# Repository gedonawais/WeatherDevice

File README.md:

# Weather Device - Raspberry Pi Zero 2W Setup Guide

This document explains how to set up the Raspberry Pi Zero 2W for the Weather Device project.

---

# 1. Install Raspberry Pi OS Lite (64 Bit) without Desktop

1. Download and install **Raspberry Pi OS Lite** using Raspberry Pi Imager.
2. Flash the OS to the SD card.
3. Before writing the image, configure:
   - Set username and password
   - Configure Wi-Fi (optional)

Boot the Raspberry Pi.

---

# 2. Configure Raspberry Pi

## 2.1 Enable Automatic Login

Open the Raspberry Pi configuration tool:

```bash
sudo raspi-config
```
Set System Date and Time and WLAN Country in the Localisation menu if not setup during installaion of RPi image

Set Wireless LAN SSID and Password (for wifi)

Navigate to:
```
System Options
    → Auto Login
        → Console Autologin
```

Select console auto login.

This allows the Raspberry Pi to automatically log in after boot.

---

## 2.2 Disable sudo Password Requirement

Navigate to:
```
System Options
    → Admin Password
        → Disable
```

This allows scripts and services to execute sudo commands without requiring a password.

---

# 3. Configure Network

## 3.1 Connect to Wi-Fi

Open Raspberry Pi configuration:

```bash
sudo raspi-config
```

Navigate to:

```
System Options
    → Wireless LAN
```

Enter:

- Wi-Fi SSID
- Wi-Fi password

Reboot if required.

---

# 4. Install Required Software

## 4.1 Update Package List

Run:

```bash
sudo apt update
```

---

## 4.2 Install Git

Install Git:

```bash
sudo apt install git -y
```

Verify installation:

```bash
git --version
```

---

# 5. Download Weather Device Repository
If you wish to enable Wifi use the following commands

```bash
sudo systemctl enable NetworkManager.service
sudo systemctl start NetworkManager.service
sudo nmcli radio wifi on
```
Move to the home directory:

```bash
cd /home
```

Clone the repository:

```bash
sudo git clone <REPOSITORY_URL>
```

Example:

```bash
sudo git clone https://github.com/<username>/WeatherDevice.git
```

The project should now be available at:

```
/home/WeatherDevice
```

---

# 6. Configure Git Repository Permission

If Git shows a **"detected dubious ownership in repository"** error, run:

```bash
git config --global --add safe.directory /home/WeatherDevice
```

---

# 7. Deploy System Configuration

Run the configuration deployment script:

```bash
bash /home/WeatherDevice/Firmware/RPi/Installations/deploy_config.sh
```

This installs required system files, services, and configurations.

---

# 8. Install Python Dependencies

Run the installation script:

```bash
bash /home/WeatherDevice/Firmware/RPi/Installations/install.sh
```

This installs all required libraries and dependencies.

---

# 9. Disable Wi-Fi (Optional)
NetworkManager is already disabled so no need to run this
Disable Wi-Fi:

```bash
sudo nmcli radio wifi off
```

Check Wi-Fi status:

```bash
nmcli radio
```

---

---

# Restart Raspberry Pi

Reboot the device:

```bash
sudo reboot
```

Wait until the Raspberry Pi boots again.

---

# 10. Weather Service Management

## Start Weather Service

```bash
sudo systemctl enable weather.service
sudo systemctl start weather.service
```

---

# 12. Check Service Status

```bash
sudo systemctl status weather.service
```

---

## View Live Service Logs

To monitor real-time logs:

```bash
journalctl -u weather.service -f
```

---

## Restart Service if there are any issues in logs

After changing code:

```bash
sudo systemctl restart weather.service
```

---

## Updating the Software

To update the Weather Device software:

```bash
sudo nmcli radio wifi on
cd /home/WeatherDevice
```

Download the latest changes:

```bash
sudo git pull
sudo nmcli radio wifi off
```

Restart the service:

```bash
sudo systemctl restart weather.service
```

# Setup Complete

The Raspberry Pi Zero 2W is now configured and ready to run the Weather Device application.

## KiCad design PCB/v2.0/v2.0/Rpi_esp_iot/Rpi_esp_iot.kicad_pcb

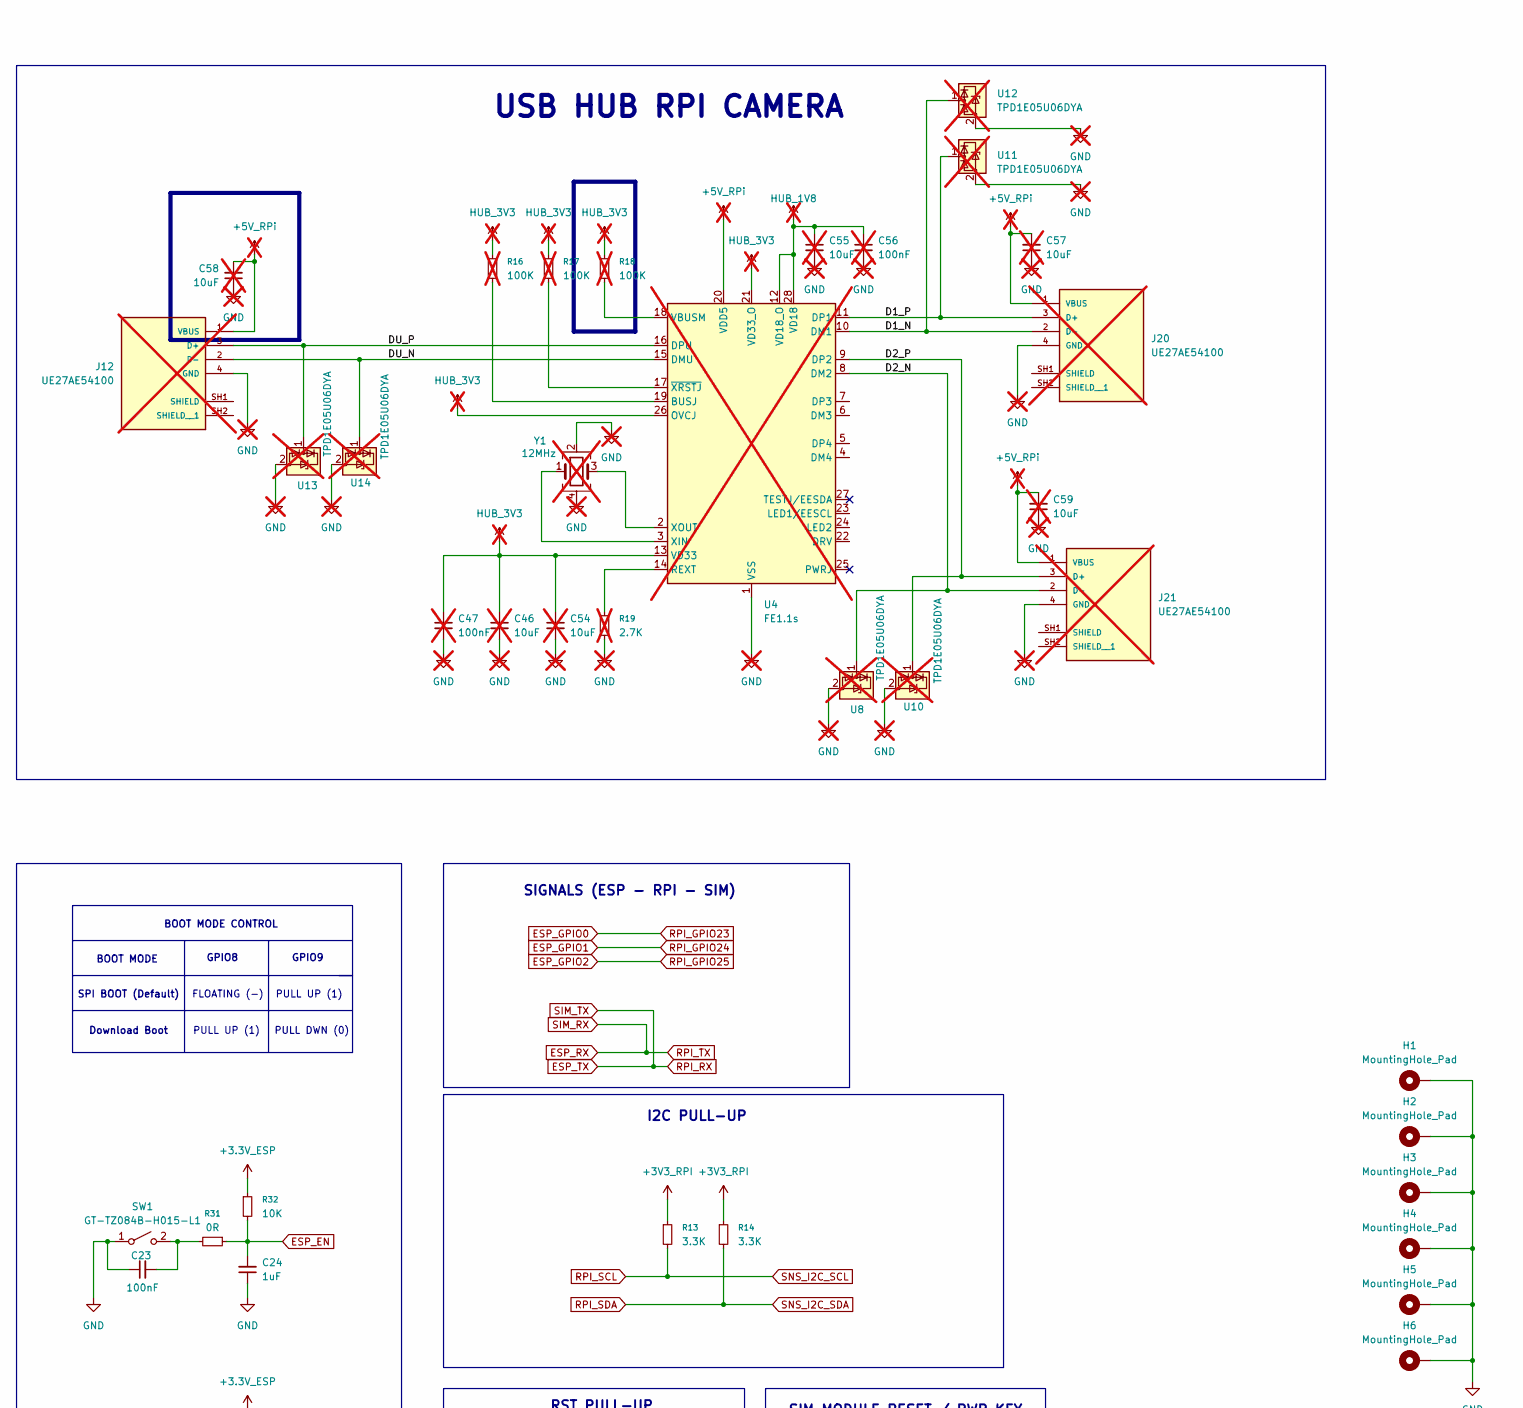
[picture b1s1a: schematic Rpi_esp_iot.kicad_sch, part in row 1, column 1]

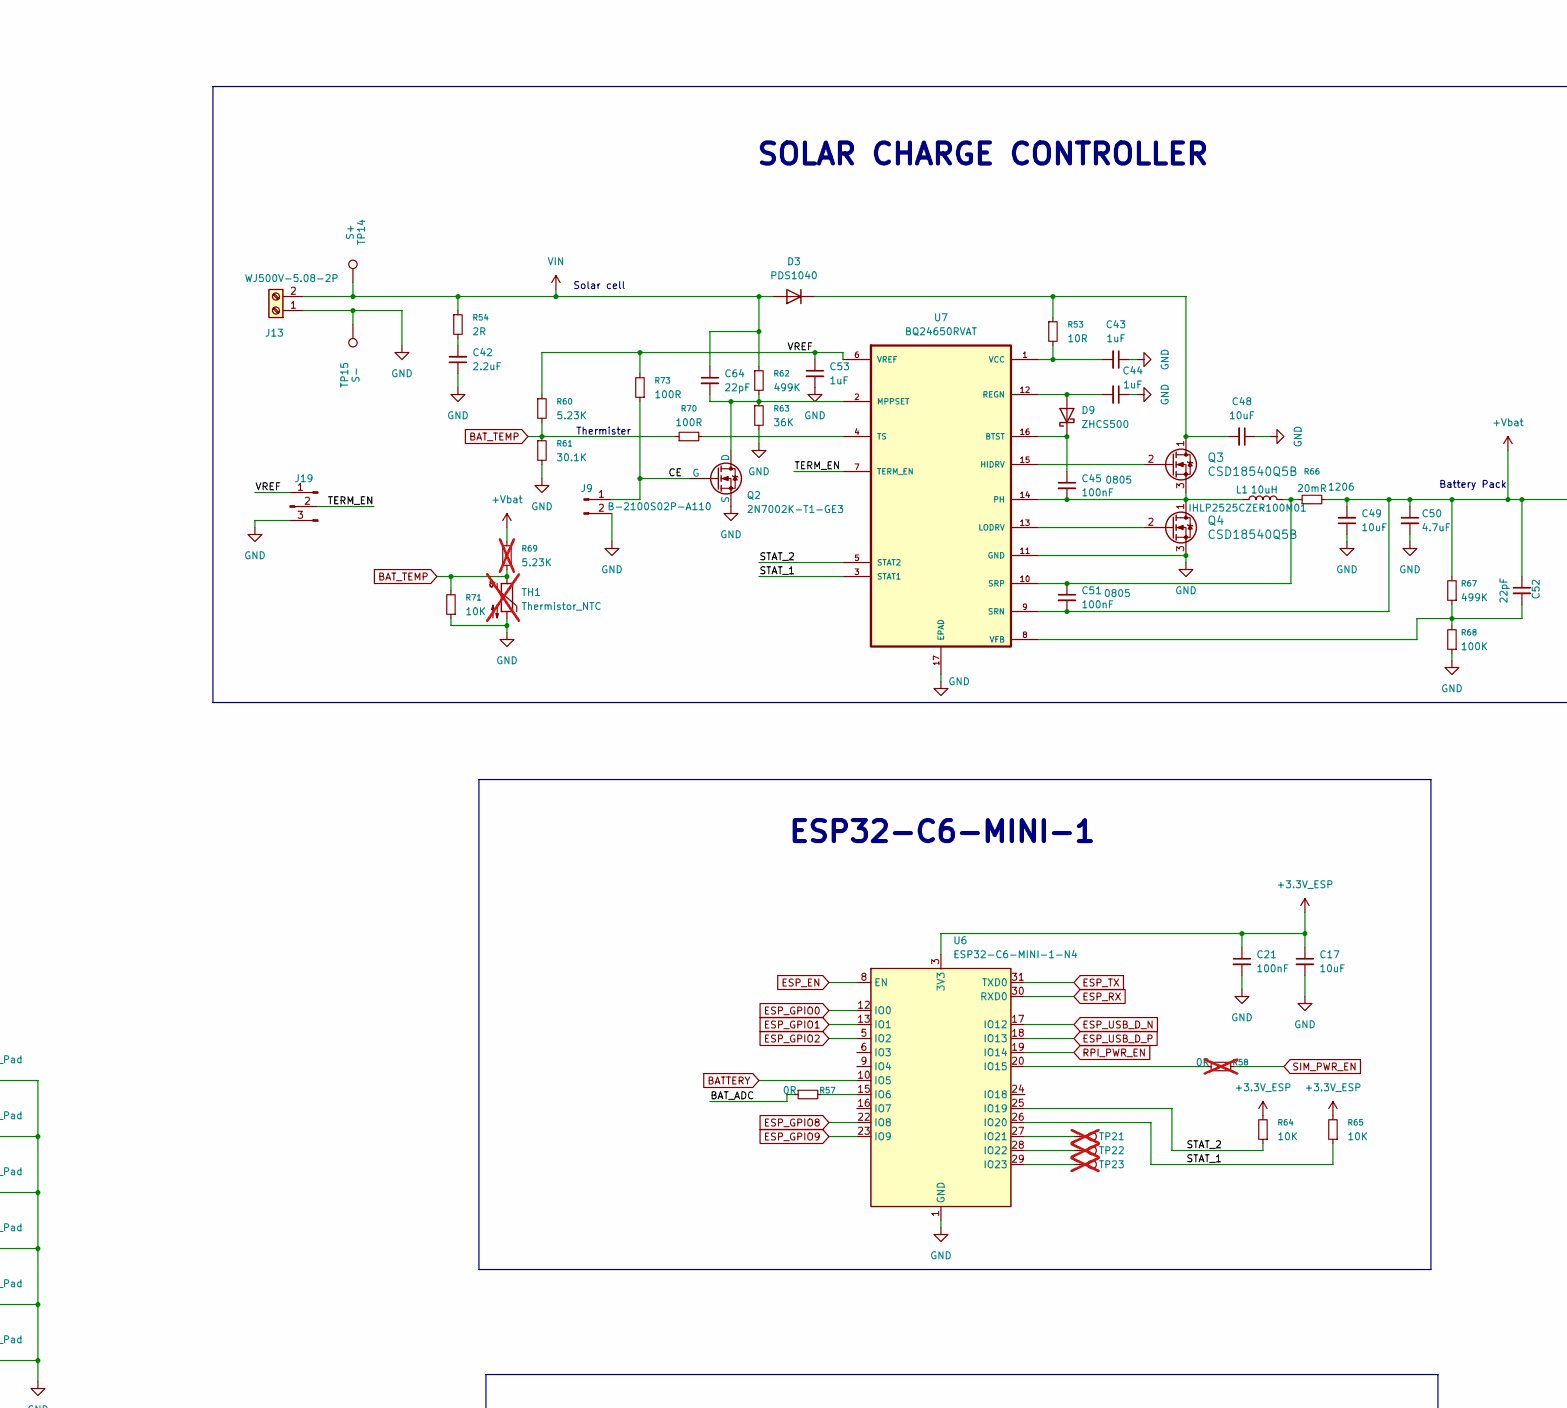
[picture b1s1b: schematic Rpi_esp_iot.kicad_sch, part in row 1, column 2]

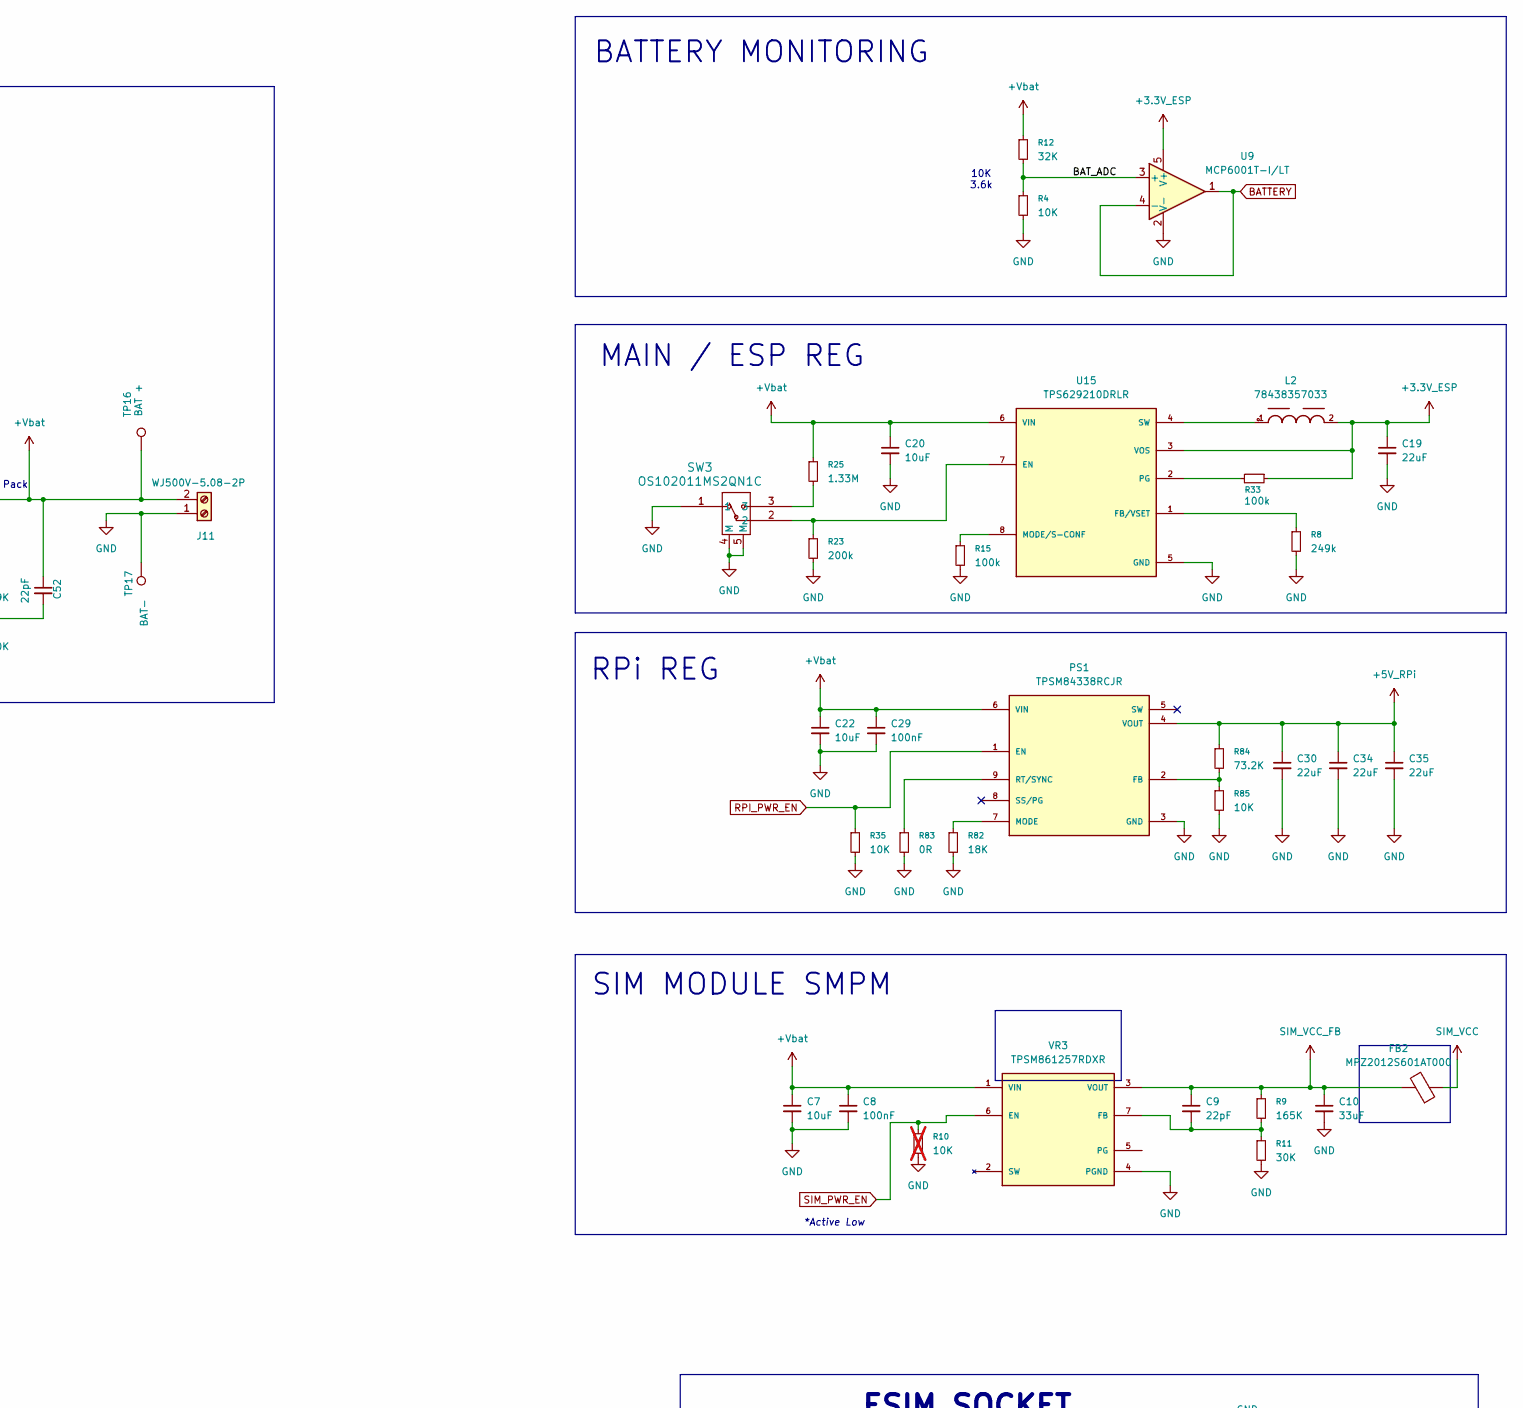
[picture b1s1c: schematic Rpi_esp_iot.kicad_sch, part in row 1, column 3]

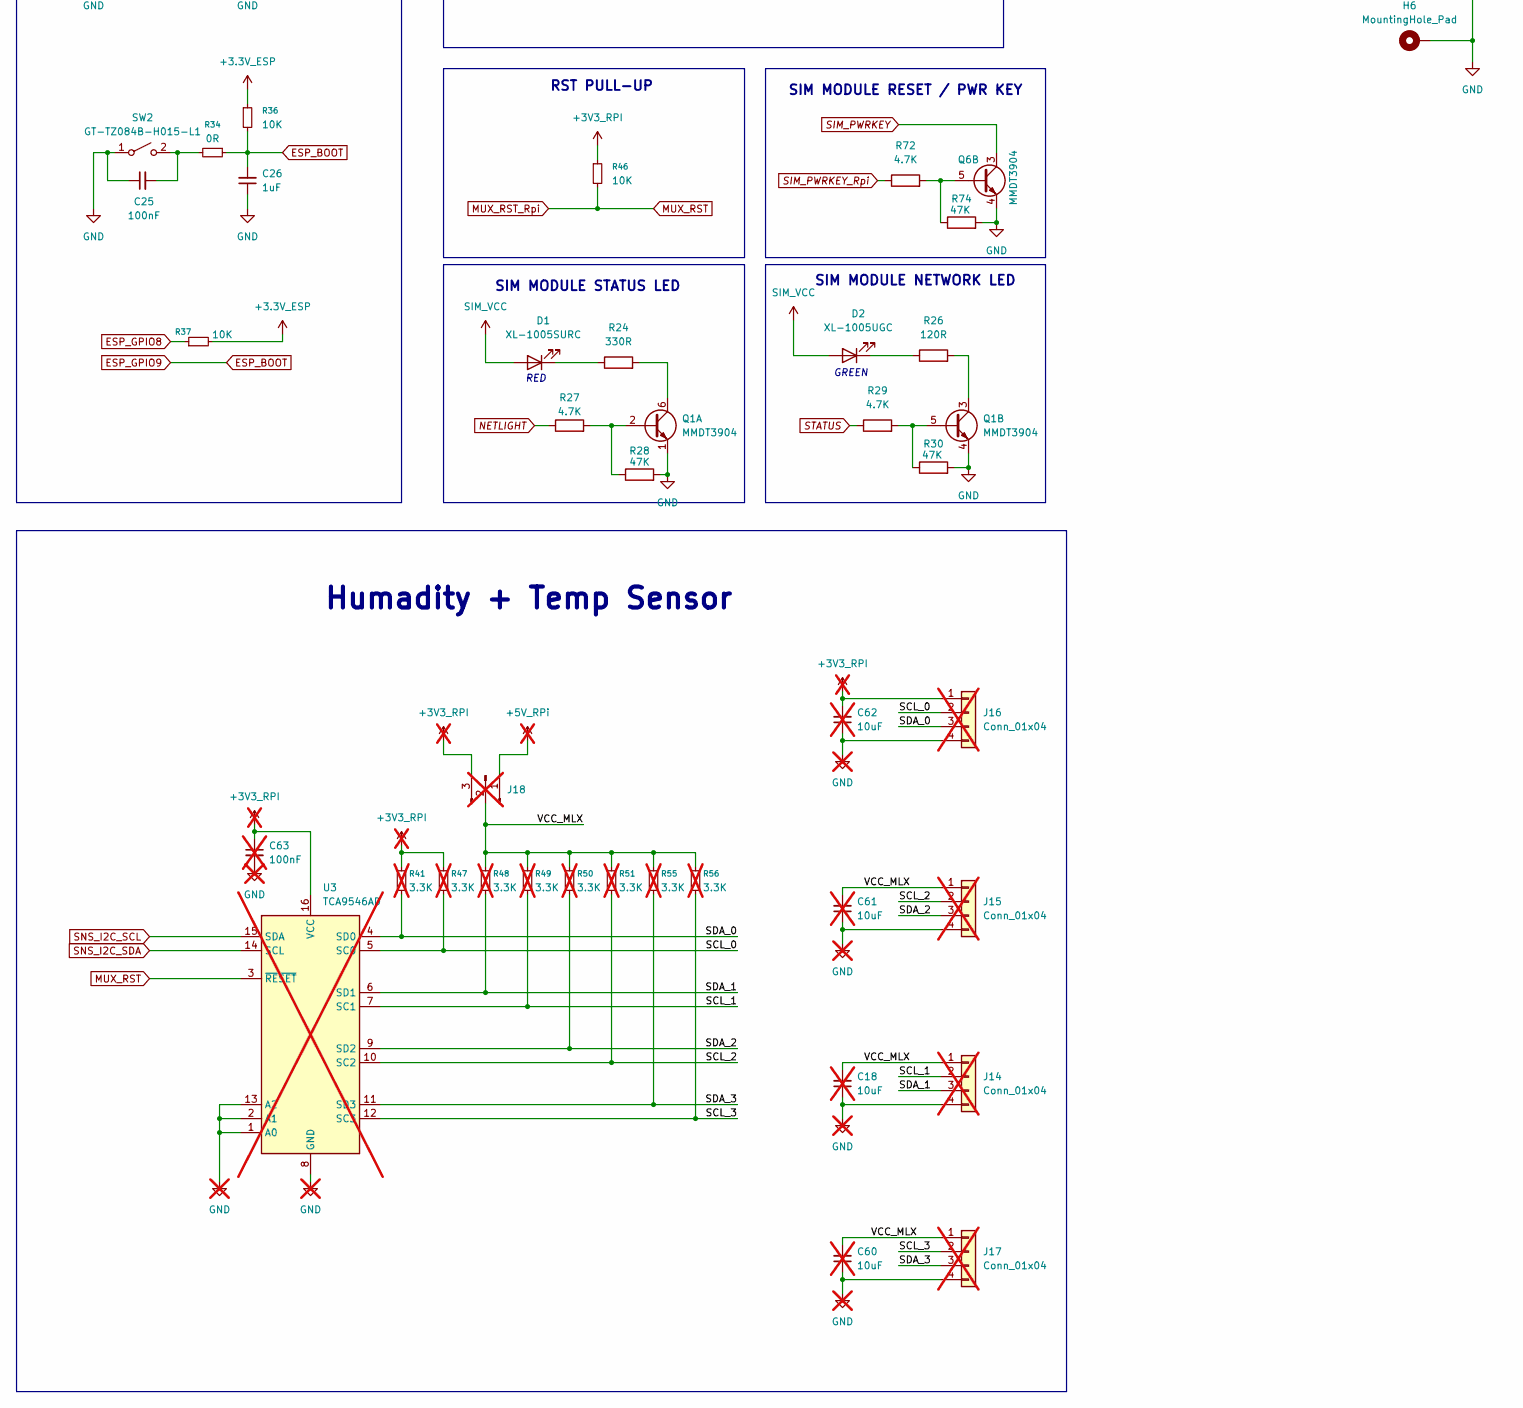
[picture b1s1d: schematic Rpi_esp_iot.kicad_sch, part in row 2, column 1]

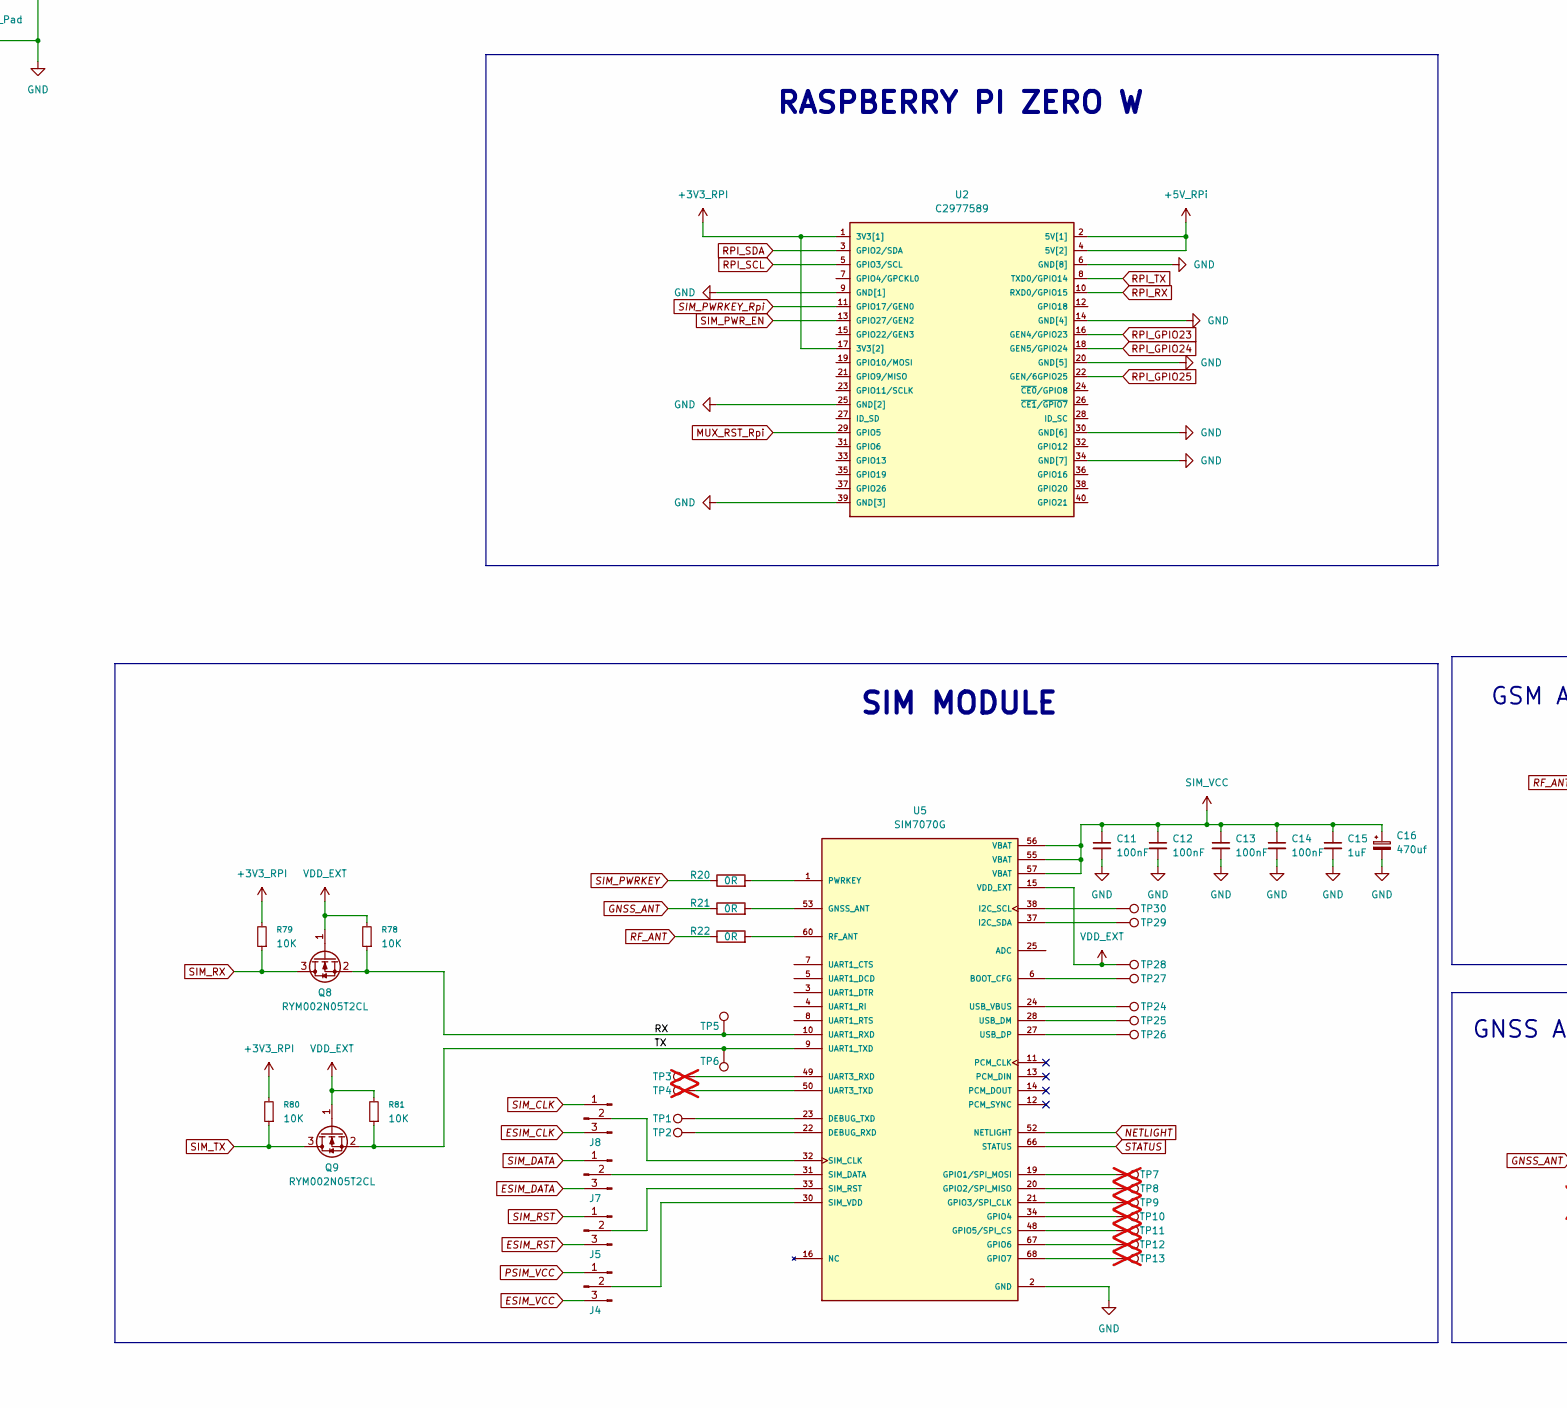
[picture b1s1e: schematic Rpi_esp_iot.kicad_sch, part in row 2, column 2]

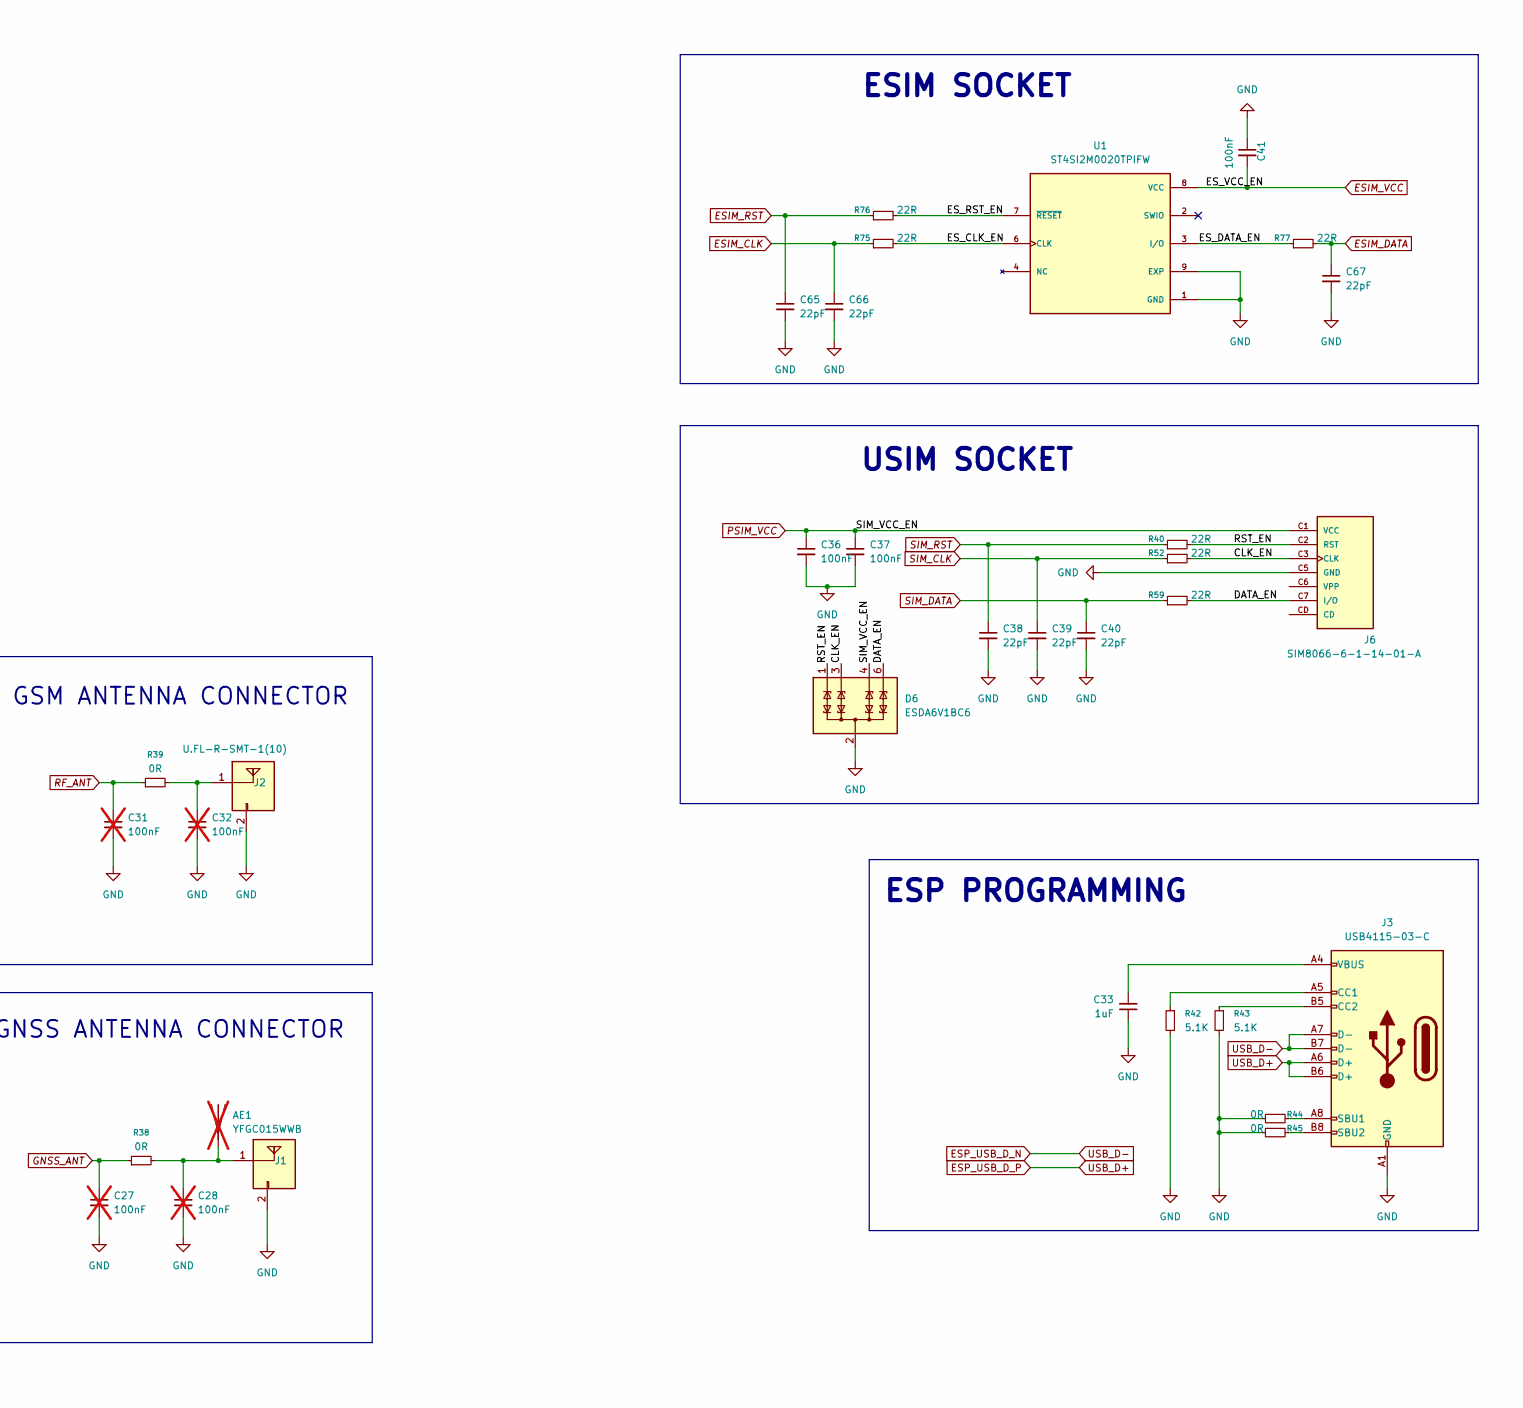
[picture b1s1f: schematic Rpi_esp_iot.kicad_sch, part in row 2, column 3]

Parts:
AE1: YFGC015WWB; not fitted
C7, C17, C22: 10uF; C_1206_3216Metric; Manufacturer Part Number CL05A106MP5NUNC
C8, C11, C12, C13, C14, C21, C23, C25, C36, C37, C41: 100nF; C_0402_1005Metric; Manufacturer Part Number CC0402KRX7R7BB104
C9: 22pF; C_0402_1005Metric; Manufacturer Part Number GRM1555C1H220JA01D
C10: 33uF; C_1206_3216Metric; Manufacturer Part Number CL05C330JB5NNNC
C15, C24, C26, C33: 1uF; C_0402_1005Metric; Manufacturer Part Number CL05A105KP5NNNC
C16: 470uf; CP_EIA-7343-15_Kemet-W_HandSolder; Manufacturer Part Number TAJD477K006RNJ
C18, C57, C58, C59, C60, C61, C62: 10uF; C_1210_3225Metric_Pad1.33x2.70mm_HandSolder; Manufacturer Part Number CC1210KKX7R9BB106; not fitted
C19, C30, C34, C35: 22uF; C_1206_3216Metric; Manufacturer Part Number CL05C330JB5NNNC
C20: 10uF; C_1206_3216Metric; Manufacturer Part Number CL05C330JB5NNNC
C27, C28, C31, C32, C47, C56, C63: 100nF; C_0402_1005Metric; Manufacturer Part Number CC0402KRX7R7BB104; not fitted
C29: 100nF; C_0805_2012Metric; Manufacturer Part Number CC0402KRX7R7BB104
C38, C39, C40, C65, C66, C67: 22pF; C_0402_1005Metric; Manufacturer Part Number CL05A226MQ5QUNC
C42: 2.2uF; C_1210_3225Metric_Pad1.33x2.70mm_HandSolder; Manufacturer Part Number C1210C225K1RACAUTO
C43, C44, C53: 1uF; C_0805_2012Metric_Pad1.18x1.45mm_HandSolder; Manufacturer Part Number C0805C105K5RACAUTO
C45, C51: 100nF; R_0805_2012Metric; Manufacturer Part Number CC0805KRX7R9BB104
C46, C54, C55: 10uF; C_0402_1005Metric; Manufacturer Part Number CL05A106MP5NUNC; not fitted
C48, C49: 10uF; C_1210_3225Metric_Pad1.33x2.70mm_HandSolder; Manufacturer Part Number CC1210KKX7R9BB106
C50: 4.7uF; C_1210_3225Metric_Pad1.33x2.70mm_HandSolder; Manufacturer Part Number CL32B475KBUYNNE
C52, C64: 22pF; C_0603_1608Metric_Pad1.08x0.95mm_HandSolder; Manufacturer Part Number C0603C220K5RACAUTO
D1: XL-1005SURC; LED_0402_1005Metric_Pad0.77x0.64mm_HandSolder; Manufacturer Part Number XL-1005SURC
D2: XL-1005UGC; LED_0402_1005Metric_Pad0.77x0.64mm_HandSolder; Manufacturer Part Number XL-1005UGC
D3: PDS1040; D_PowerDI-5; Manufacturer Part Number PDS1040-13
D6: ESDA6V1BC6; SOT-23-6_Handsoldering; Manufacturer Part Number ESDA6V1BC6
D9: ZHCS500; SOT-23-3; Manufacturer Part Number ZHCS500TA
FB2: MPZ2012S601AT000; C_0805_2012Metric; Manufacturer Part Number MPZ2012S601AT000
H1, H2, H3, H4, H5, H6: MountingHole_Pad; MountingHole_3.2mm_M3_DIN965_Pad
J1, J2: U.FL-R-SMT-1(10); U.FL_Hirose_U.FL-R-SMT-1_Vertical; Manufacturer Part Number U.FL-R-SMT-1(80)
J3: USB4115-03-C; USB4115-03-C_GCT; Manufacturer Part Number USB4115-03-C
J4, J5, J7, J8, J19: MTP220-1103S1; PinHeader_1x03_P2.00mm_Vertical
J6: SIM8066-6-1-14-01-A; GCT_SIM8066-6-1-14-01-A_REVA; PARTREV REVA; DigiKey_Part_Number 2073-SIM8066-6-1-14-01-ACT-ND
J9: B-2100S02P-A110; PinSocket_1x02_P2.54mm_Vertical
J11, J13: WJ500V-5.08-2P; TerminalBlock_bornier-2_P5.08mm
J12, J20, J21: UE27AE54100; AMPHENOL_UE27AE54100; PARTREV G; not fitted
J14, J15, J16, J17: Conn_01x04; JST_PH_S4B-PH-K_1x04_P2.00mm_Horizontal; not fitted
J18: MTP220-1103S1; PinHeader_1x03_P2.00mm_Vertical; not fitted
L1: IHLP2525CZER100M01; L_Vishay_IHLP-2525; Manufacturer Part Number 10uH
L2: 78438357033; WE-MAIA_4030
PS1: TPSM84338RCJR; CONV_TPSM84338RCJR; PARTREV November 2024
Q1, Q6: MMDT3904; SOT-363_SC-70-6; Manufacturer Part Number MMDT3904
Q2: 2N7002K-T1-GE3; SOT-23_Handsoldering; Manufacturer Part Number 2N7002K-T1-GE3
Q3, Q4: CSD18540Q5B; Manufacturer Part Number CSD18540Q5B
Q8, Q9: RYM002N05T2CL; SOT-723
R4, R32, R35, R36, R37, R46, R64, R65, R71, R78, R79, R80, R81: 10K; R_0402_1005Metric; Manufacturer Part Number RC0402FR-0710KL
R8: 249k; R_0402_1005Metric; Manufacturer Part Number RC0402FR-0710KL
R9: 165K; R_0402_1005Metric; Manufacturer Part Number RK73H1ET1653F-CN
R10: 10K; R_0402_1005Metric; Manufacturer Part Number RC0402FR-0710KL; not fitted
R11: 30K; R_0402_1005Metric; Manufacturer Part Number RC0402FR-0730KL
R12: 32K; R_0402_1005Metric; Manufacturer Part Number TNPW040232K0BEED
R13, R14: 3.3K; R_0402_1005Metric; Manufacturer Part Number RC0402FR-0710KL
R15, R33: 100k; R_0402_1005Metric; Manufacturer Part Number RC0402FR-0710KL
R16, R17, R18: 100K; R_0402_1005Metric; Manufacturer Part Number RC0402FR-0710KL; not fitted
R19: 2.7K; R_0402_1005Metric; Manufacturer Part Number RC0402FR-0710KL; not fitted
R20, R21, R22, R31, R34, R38, R39, R44, R45, R57: 0R; R_0402_1005Metric; Manufacturer Part Number RC0402FR-070RL
R23: 200k; R_0402_1005Metric; Manufacturer Part Number RC0402FR-0710KL
R24: 330R; R_0402_1005Metric; Manufacturer Part Number RC0402FR-07330RL
R25: 1.33M; R_0402_1005Metric; Manufacturer Part Number RC0402FR-0710KL
R26: 120R; R_0402_1005Metric; Manufacturer Part Number RC0402FR-07120RL
R27, R29, R72: 4.7K; R_0402_1005Metric; Manufacturer Part Number RC0402FR-074K7L
R28, R30, R74: 47K; R_0402_1005Metric; Manufacturer Part Number RC0402FR-0747KL
R40, R52, R59, R75, R76, R77: 22R; R_0402_1005Metric; Manufacturer Part Number RC0402FR-070RL
R41, R47, R48, R49, R50, R51, R55, R56: 3.3K; R_0402_1005Metric; Manufacturer Part Number RC0402FR-0710KL; not fitted
R42, R43: 5.1K; R_0402_1005Metric; Manufacturer Part Number RC0402FR-0710KL
R53: 10R; R_1206_3216Metric_Pad1.30x1.75mm_HandSolder; Manufacturer Part Number RC1206FR-0710RL
R54: 2R; R_2512_6332Metric_Pad1.40x3.35mm_HandSolder; Manufacturer Part Number MFCR2512F2R00Q9R
R58: 0R; R_0402_1005Metric; Manufacturer Part Number RC0402FR-070RL; not fitted
R60: 5.23K; R_0402_1005Metric; Manufacturer Part Number ARG02BTC5231
R61: 30.1K; R_0402_1005Metric; Manufacturer Part Number 0402WGF3012TCE
R62, R67: 499K; R_0402_1005Metric; Manufacturer Part Number RC0402FR-07499KL
R63: 36K; R_0402_1005Metric; Manufacturer Part Number FRC0402F3602TS
R66: 20mR; R_1206_3216Metric_Pad1.30x1.75mm_HandSolder; Manufacturer Part Number JER1206F1R020
R68: 100K; R_0402_1005Metric; Manufacturer Part Number RC0402FR-07100KL
R69: 5.23K; R_0402_1005Metric; Manufacturer Part Number ARG02BTC5231; not fitted
R70, R73: 100R; R_0402_1005Metric; Manufacturer Part Number RC0402FR-0710KL
R82: 18K; R_0402_1005Metric; Manufacturer Part Number RC0402FR-0710KL
R83: 0R; R_0402_1005Metric; Manufacturer Part Number RC0402FR-0710KL
R84: 73.2K; R_0402_1005Metric; Manufacturer Part Number RC0402FR-07220KL
R85: 10K; R_0402_1005Metric; Manufacturer Part Number RC0402FR-0730KL
SW1, SW2: GT-TZ084B-H015-L1; SW_SPST_SKQG_WithStem; Manufacturer Part Number GT-TZ084B-H015-L1
SW3: OS102011MS2QN1C; SW-TH_OS102011MS2QN1
TH1: Thermistor_NTC; R_0402_1005Metric_Pad0.72x0.64mm_HandSolder; Manufacturer Part Number FNTC0402X103F3380FB; not fitted
TP1, TP2, TP5, TP6, TP24, TP25, TP26, TP27, TP28, TP29, TP30: TestPoint; TestPoint_Pad_D1.5mm
TP3, TP4, TP7, TP8, TP9, TP10, TP11, TP12, TP13, TP21, TP22, TP23: TestPoint; TestPoint_Pad_2.0x2.0mm; not fitted
TP14: S+; TestPoint_Pad_2.0x2.0mm
TP15: S-; TestPoint_Pad_2.0x2.0mm
TP16: BAT +; TestPoint_Pad_2.0x2.0mm
TP17: BAT-; TestPoint_Pad_2.0x2.0mm
U1: ST4SI2M0020TPIFW; SON127P500X600X100-9N; PARTREV 5
U2: C2977589; Raspberry_Pi_Zero_Socketed_THT_FaceDown_MountingHoles; Manufacturer Part Number RASPBERRYPI-ZERO
U3: TCA9546AD; SOIC-16_3.9x9.9mm_P1.27mm; not fitted
U4: FE1.1s; SSOP-28_3.9x9.9mm_P0.635mm; not fitted
U5: SIM7070G; MODULE_SIM7070G; PARTREV V1.03; DigiKey_Part_Number 3781-SIM7070G-ND
U6: ESP32-C6-MINI-1-N4; ESP32-C6-MINI-1; Manufacturer Part Number ESP32-C6-MINI-1-N4
U7: BQ24650RVAT; QFN50P350X350X100-17N; Manufacturer Part Number BQ24650RVAT; DigiKey_Part_Number 296-27699-1-ND
U8, U10, U11, U12, U13, U14: TPD1E05U06DYA; D_SOD-523; not fitted
U9: MCP6001T-I/LT; SOT-353_SC-70-5
U15: TPS629210DRLR; SOT50P160X60-8N; PARTREV B; DigiKey_Part_Number 296-TPS629210DRLRCT-ND
VR3: TPSM861257RDXR; VREG_TPSM863252RDXR; PARTREV B; DigiKey_Part_Number 296-TPSM861257RDXRCT-ND
Y1: 12MHz; Crystal_SMD_3225-4Pin_3.2x2.5mm; not fitted

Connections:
+3.3V_ESP: C17.1, C19.1, C21.1, L2.2, R32.1, R33.1, R36.1, R37.2, R64.2, R65.2, U6.3 (3V3), U9.5 (V+), U15.3 (VOS)
+3V3_RPI: C62.2, C63.1, J16.1, J18.3, R13.1, R14.1, R41.1, R46.1, R47.1, R79.2, R80.2, U2.1 (3V3[1]), U2.17 (3V3[2]), U3.16 (VCC)
+5V_RPi: C30.1, C34.1, C35.1, C57.2, C58.2, C59.2, J12.1 (VBUS), J18.1, J20.1 (VBUS), J21.1 (VBUS), PS1.4 (VOUT), R84.1, U2.2 (5V[1]), U2.4 (5V[2]), U4.20 (VDD5)
+Vbat: C7.1, C8.1, C20.1, C22.1, C29.1, C49.2, C50.1, C51.2, C52.1, J11.2, PS1.6 (VIN), R12.1, R25.1, R66.2, R67.2, R69.1, TP16.1 (1_1), U7.9 (SRN), U15.6 (VIN), VR3.1 (VIN)
/BAT_ADC: R4.1, R12.2, R57.1, U9.3 (+)
/CE: J9.1, Q2.2 (G), R73.1
/CLK_EN: D6.3 (TVS2), J6.C3 (CLK), R52.2
/D1_N: J20.2 (D-), U4.10 (DM1), U12.1 (I/O)
/D1_P: J20.3 (D+), U4.11 (DP1), U11.1 (I/O)
/D2_N: J21.2 (D-), U4.8 (DM2), U8.1 (I/O)
/D2_P: J21.3 (D+), U4.9 (DP2), U10.1 (I/O)
/DATA_EN: D6.6 (TVS4), J6.C7 (I/O), R59.2
/DU_N: J12.2 (D-), U4.15 (DMU), U14.1 (I/O)
/DU_P: J12.3 (D+), U4.16 (DPU), U13.1 (I/O)
/ES_CLK_EN: R75.2, U1.6 (CLK)
/ES_DATA_EN: R77.1, U1.3 (I/O)
/ES_RST_EN: R76.2, U1.7 (~RESET)
/RST_EN: D6.1 (TVS1), J6.C2 (RST), R40.2
/RX: Q8.2 (S), R78.1, TP5.1 (1_1), U5.10 (UART1_RXD)
/SCL_0: J16.2, R47.2, U3.5 (SC0)
/SCL_1: J14.2, R49.2, U3.7 (SC1)
/SCL_2: J15.2, R51.2, U3.10 (SC2)
/SCL_3: J17.2, R56.2, U3.12 (SC3)
/SDA_0: J16.3, R41.2, U3.4 (SD0)
/SDA_1: J14.3, R48.2, U3.6 (SD1)
/SDA_2: J15.3, R50.2, U3.9 (SD2)
/SDA_3: J17.3, R55.2, U3.11 (SD3)
/STAT_1: R65.1, U6.26 (IO20), U7.3 (STAT1)
/STAT_2: R64.1, U6.25 (IO19), U7.5 (STAT2)
/TERM_EN: J19.2, U7.7 (TERM_EN)
/TX: Q9.2 (S), R81.1, TP6.1 (1_1), U5.9 (UART1_TXD)
/VCC_MLX: C18.2, C60.2, C61.2, J14.1, J15.1, J17.1, J18.2, R48.1, R49.1, R50.1, R51.1, R55.1, R56.1
/VREF: C53.1, J19.1, R60.1, R73.2, U7.6 (VREF)
BATTERY: U6.10 (IO5), U9.1, U9.4 (-)
BAT_TEMP: R60.2, R61.1, R69.2, R70.1, R71.2, TH1.1
ESIM_CLK: C66.1, J8.3, R75.1
ESIM_DATA: C67.1, J7.3, R77.2
ESIM_RST: C65.1, J5.3, R76.1
ESIM_VCC: C41.2, J4.3, U1.8 (VCC)
ESP_BOOT: C26.2, R34.1, R36.2, U6.23 (IO9)
ESP_EN: C24.2, R31.1, R32.2, U6.8 (EN)
ESP_GPIO0: U2.16 (GEN4/GPIO23), U6.12 (IO0)
ESP_GPIO1: U2.18 (GEN5/GPIO24), U6.13 (IO1)
ESP_GPIO2: U2.22 (GEN/6GPIO25), U6.5 (IO2)
ESP_GPIO8: R37.1, U6.22 (IO8)
ESP_RX: Q8.3 (D), R79.1, U2.8 (TXD0/GPIO14), U6.30 (RXD0)
ESP_TX: Q9.3 (D), R80.1, U2.10 (RXD0/GPIO15), U6.31 (TXD0)
ESP_USB_D_N: J3.A7 (D-), J3.B7 (D-), U6.17 (IO12)
ESP_USB_D_P: J3.A6 (D+), J3.B6 (D+), U6.18 (IO13)
GND: C7.2, C8.2, C10.2, C11.2, C12.2, C13.2, C14.2, C15.2, C16.2, C17.2, C18.1, C19.2, C20.2, C21.2, C22.2, C23.1, C24.1, C25.1, C26.1, C27.2, C28.2, C29.2, C30.2, C31.2, C32.2, C33.1, C34.2, C35.2, C36.2, C37.2, C38.2, C39.2, C40.2, C41.1, C42.1, C43.1, C44.1, C46.2, C47.2, C48.1, C49.1, C50.2, C53.2, C54.2, C55.2, C56.2, C57.1, C58.1, C59.1, C60.1, C61.1, C62.1, C63.2, C65.2, C66.2, C67.2, D6.2 (COM), D6.5 (COM), H1.1 (1_1), H2.1 (1_1), H3.1 (1_1), H4.1 (1_1), H5.1 (1_1), H6.1 (1_1), J1.2, J2.2, J3.A1 (GND), J3.A12 (GND), J3.B1 (GND), J3.B12 (GND), J6.C5 (GND), J6.G1 (GND), J6.G2 (GND), J6.G3 (GND), J6.G4 (GND), J9.2, J11.1, J12.4 (GND), J13.1, J14.4, J15.4, J16.4, J17.4, J19.3, J20.4 (GND), J21.4 (GND), PS1.3 (GND), Q1.1 (E1), Q1.4 (E2), Q2.3 (S), Q4.3, Q6.4 (E2), R4.2, R8.2, R10.2, R11.2, R15.2, R19.2, R23.2, R28.2, R30.2, R35.2, R42.2, R43.2, R44.1, R45.1, R61.2, R63.2, R68.1, R71.1, R74.2, R82.2, R83.2, R85.2, SW1.1 (A), SW2.1 (A), SW3.1, SW3.4 (M), SW3.5 (M), TH1.2, TP15.1 (1_1), TP17.1 (1_1), U1.1 (GND), U1.9 (EXP), U2.6 (GND[8]), U2.9 (GND[1]), U2.14 (GND[4]), U2.20 (GND[5]), U2.25 (GND[2]), U2.30 (GND[6]), U2.34 (GND[7]), U2.39 (GND[3]), U3.1 (A0), U3.2 (A1), U3.8 (GND), U3.13 (A2), U4.1 (VSS), U5.2 (GND), U5.17 (GND), U5.18 (GND), U5.29 (GND), U5.39 (GND), U5.45 (GND), U5.46 (GND), U5.54 (GND), U5.58 (GND), U5.59 (GND), U5.61 (GND), U5.62 (GND), U5.63 (GND), U5.64 (GND), U5.65 (GND), U6.1 (GND), U6.2 (GND), U6.11 (GND), U6.14 (GND), U6.36 (GND), U6.37 (GND), U6.38 (GND), U6.39 (GND), U6.40 (GND), U6.41 (GND), U6.42 (GND), U6.43 (GND), U6.44 (GND), U6.45 (GND), U6.46 (GND), U6.47 (GND), U6.48 (GND), U6.49 (GND), U6.50 (GND), U6.51 (GND), U6.52 (GND), U6.53 (GND), U7.11 (GND), U7.17 (EPAD), U8.2 (GND), U9.2 (V-), U10.2 (GND), U11.2 (GND), U12.2 (GND), U13.2 (GND), U14.2 (GND), U15.5 (GND), VR3.4 (PGND), Y1.2, Y1.4
GNSS_ANT: C27.1, R21.1, R38.1
HUB_1V8: C55.1, C56.1, U4.12 (VD18_O), U4.28 (VD18)
HUB_3V3: C46.1, C47.1, C54.1, R16.1, R17.1, R18.1, U4.13 (VD33), U4.21 (VD33_O), U4.26 (OVCJ)
MUX_RST: R46.2, U2.29 (GPIO5), U3.3 (~RESET)
NETLIGHT: R27.1, U5.52 (NETLIGHT)
unnamed: C33.2, J3.A4 (VBUS), J3.A9 (VBUS), J3.B4 (VBUS), J3.B9 (VBUS)
unnamed: C42.2, R54.2
unnamed: D1.1 (K), R24.1
unnamed: D2.1 (K), R26.1
unnamed: C48.2, D3.1 (K), Q3.1, R53.1
unnamed: C44.2, D9.3 (A), U7.12 (REGN)
unnamed: C45.1, D9.1 (K), U7.16 (BTST)
unnamed: AE1.1, C28.1, J1.1, R38.2
unnamed: C32.1, J2.1, R39.2
unnamed: J3.A5 (CC1), R42.1
unnamed: J3.B5 (CC2), R43.1
unnamed: J3.A8 (SBU1), R44.2
unnamed: J3.B8 (SBU2), R45.2
unnamed: J4.2, U5.30 (SIM_VDD)
unnamed: J5.2, U5.33 (SIM_RST)
unnamed: J7.2, U5.31 (SIM_DATA)
unnamed: J8.2, U5.32 (SIM_CLK)
unnamed: PS1.2 (FB), R84.2, R85.1
unnamed: PS1.7 (MODE), R82.1
unnamed: PS1.9 (RT/SYNC), R83.1
unnamed: Q1.2 (B1), R27.2, R28.1
unnamed: Q1.6 (C1), R24.2
unnamed: Q1.5 (B2), R29.2, R30.1
unnamed: Q1.3 (C2), R26.2
unnamed: C64.2, Q2.1 (D), R62.2, R63.1, U7.2 (MPPSET)
unnamed: Q6.5 (B2), R72.2, R74.1
unnamed: R25.2, SW3.3
unnamed: C23.2, R31.2, SW1.2 (B)
unnamed: C25.2, R34.2, SW2.2 (B)
unnamed: R16.2, U4.19 (BUSJ)
unnamed: R19.1, U4.14 (REXT)
unnamed: R18.2, U4.18 (VBUSM)
unnamed: U4.3 (XIN), Y1.1
unnamed: U4.2 (XOUT), Y1.3
unnamed: R17.2, U4.17 (~XRSTJ)
unnamed: TP27.1 (1_1), U5.6 (BOOT_CFG)
unnamed: TP2.1 (1_1), U5.22 (DEBUG_RXD)
unnamed: TP1.1 (1_1), U5.23 (DEBUG_TXD)
unnamed: R21.2, U5.53 (GNSS_ANT)
unnamed: TP7.1, U5.19 (GPIO1/SPI_MOSI)
unnamed: TP8.1, U5.20 (GPIO2/SPI_MISO)
unnamed: TP9.1, U5.21 (GPIO3/SPI_CLK)
unnamed: TP10.1, U5.34 (GPIO4)
unnamed: TP11.1, U5.48 (GPIO5/SPI_CS)
unnamed: TP12.1, U5.67 (GPIO6)
unnamed: TP13.1, U5.68 (GPIO7)
unnamed: TP30.1 (1_1), U5.38 (I2C_SCL)
unnamed: TP29.1 (1_1), U5.37 (I2C_SDA)
unnamed: R20.2, U5.1 (PWRKEY)
unnamed: R22.2, U5.60 (RF_ANT)
unnamed: TP3.1, U5.49 (UART3_RXD)
unnamed: TP4.1, U5.50 (UART3_TXD)
unnamed: TP25.1 (1_1), U5.28 (USB_DM)
unnamed: TP26.1 (1_1), U5.27 (USB_DP)
unnamed: TP24.1 (1_1), U5.24 (USB_VBUS)
unnamed: R57.2, U6.15 (IO6)
unnamed: R58.1, U6.20 (IO15)
unnamed: TP21.1, U6.27 (IO21)
unnamed: TP22.1, U6.28 (IO22)
unnamed: TP23.1, U6.29 (IO23)
unnamed: Q3.2, U7.15 (HIDRV)
unnamed: Q4.2, U7.13 (LODRV)
unnamed: C45.2, L1.1, Q3.3, Q4.1, U7.14 (PH)
unnamed: C51.1, L1.2, R66.1, U7.10 (SRP)
unnamed: R70.2, U7.4 (TS)
unnamed: C43.2, R53.2, U7.1 (VCC)
unnamed: C52.2, R67.1, R68.2, U7.8 (VFB)
unnamed: R23.1, SW3.2, U15.7 (EN)
unnamed: R8.1, U15.1 (FB/VSET)
unnamed: R15.1, U15.8 (MODE/S-CONF)
unnamed: R33.2, U15.2 (PG)
unnamed: L2.1, U15.4 (SW)
unnamed: C9.2, R9.2, R11.1, VR3.7 (FB)
PSIM_VCC: C36.1, C37.1, D6.4 (TVS3), J4.1, J6.C1 (VCC)
RF_ANT: C31.1, R22.1, R39.1
RPI_PWR_EN: PS1.1 (EN), R35.1, U6.19 (IO14)
RPI_SCL: R13.2, U2.5 (GPIO3/SCL), U3.15 (SDA)
RPI_SDA: R14.2, U2.3 (GPIO2/SDA), U3.14 (SCL)
SIM_CLK: C39.1, J8.1, R52.1
SIM_DATA: C40.1, J7.1, R59.1
SIM_PWRKEY: Q6.3 (C2), R20.1
SIM_PWRKEY_Rpi: R72.1, U2.11 (GPIO17/GEN0)
SIM_PWR_EN: R10.1, R58.2, U2.13 (GPIO27/GEN2), VR3.6 (EN)
SIM_RST: C38.1, J5.1, R40.1
SIM_VCC: C11.1, C12.1, C13.1, C14.1, C15.1, C16.1, D1.2 (A), D2.2 (A), FB2.1, U5.55 (VBAT), U5.56 (VBAT), U5.57 (VBAT)
SIM_VCC_FB: C9.1, C10.1, FB2.2, R9.1, VR3.3 (VOUT)
STATUS: R29.1, U5.66 (STATUS)
VDD_EXT: Q8.1 (G), Q9.1 (G), R78.2, R81.2, TP28.1 (1_1), U5.15 (VDD_EXT)
VIN: C64.1, D3.2 (A), J13.2, R54.1, R62.1, TP14.1 (1_1)

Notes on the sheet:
GPIO9
SIGNALS (ESP - RPI - SIM)
PULL UP (1)
GSM ANTENNA CONNECTOR
SIM MODULE SMPM
GNSS ANTENNA CONNECTOR
BOOT MODE CONTROL
Solar cell
ESP32-C6-MINI-1
SOLAR CHARGE CONTROLLER
RPi REG
RED
I2C PULL-UP
RST PULL-UP
SIM MODULE
BATTERY MONITORING
SIM MODULE RESET / PWR KEY
*Active Low
SIM MODULE NETWORK LED
Humadity + Temp Sensor
Battery Pack
RASPBERRY PI ZERO W
USB HUB RPI CAMERA
SPI BOOT (Default)
PULL DWN (0)
FLOATING (-)
GPIO8
BOOT MODE
GREEN
SIM MODULE STATUS LED
Thermister
MAIN / ESP REG
USIM SOCKET
Download Boot
ESIM SOCKET
ESP PROGRAMMING
10K 3.6k
